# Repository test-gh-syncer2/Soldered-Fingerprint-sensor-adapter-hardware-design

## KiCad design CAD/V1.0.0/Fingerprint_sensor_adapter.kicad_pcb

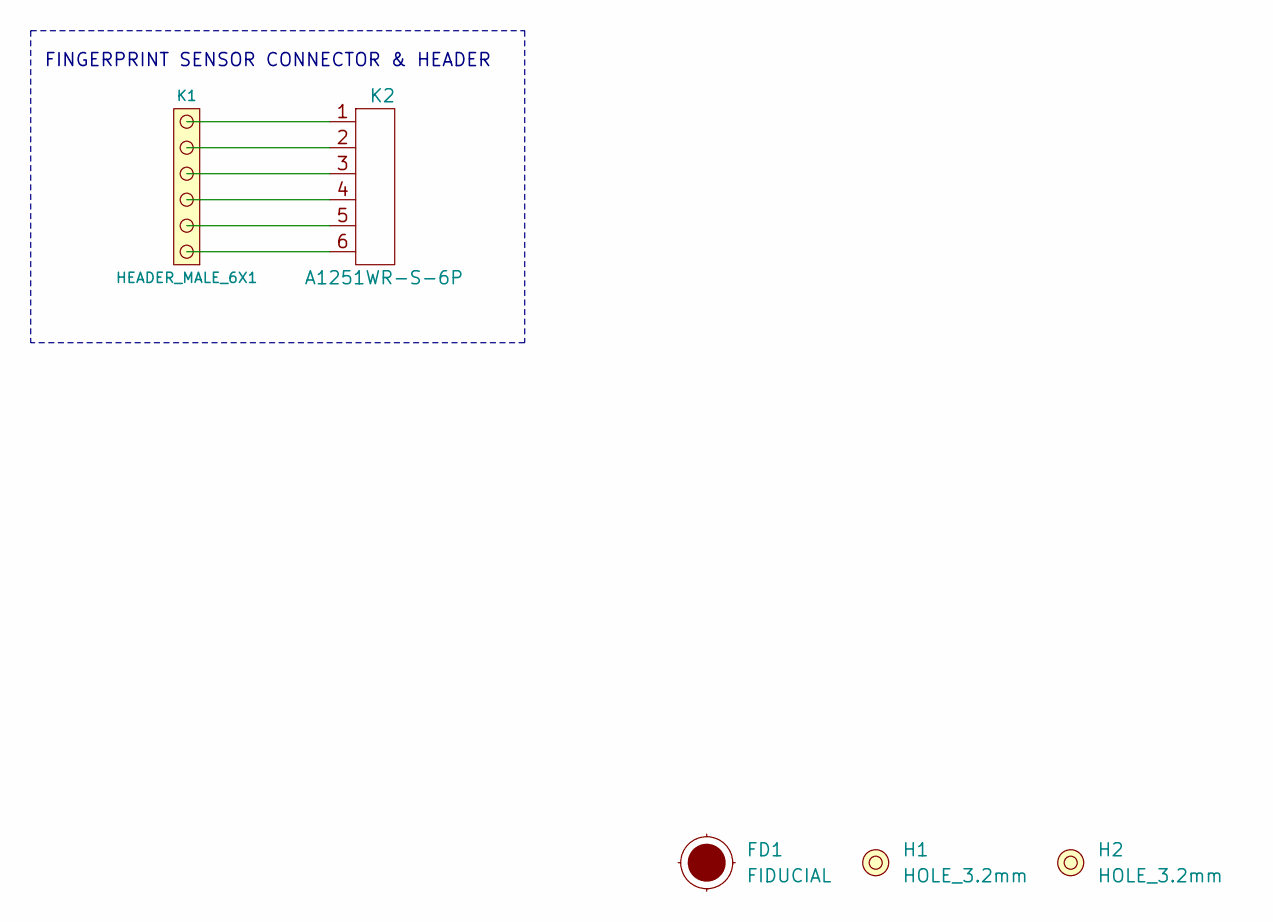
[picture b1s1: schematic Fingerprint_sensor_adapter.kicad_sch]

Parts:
FD1: FIDUCIAL; FIDUCIAL_23
H1, H2: HOLE_3.2mm
K1: HEADER_MALE_6X1
K2: A1251WR-S-6P

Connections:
unnamed: K1.1, K2.6
unnamed: K1.2, K2.5
unnamed: K1.3, K2.4
unnamed: K1.4, K2.3
unnamed: K1.5, K2.2
unnamed: K1.6, K2.1

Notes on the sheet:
FINGERPRINT SENSOR CONNECTOR & HEADER

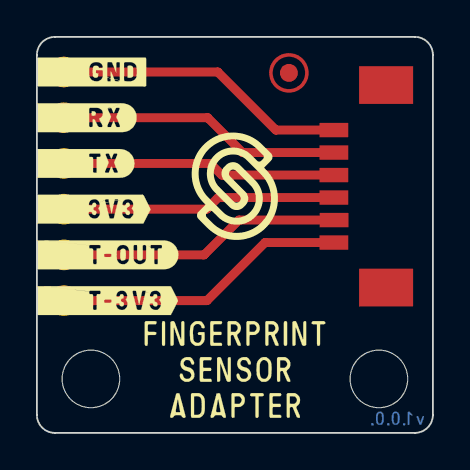
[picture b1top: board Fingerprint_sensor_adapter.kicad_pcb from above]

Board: 2 copper layers, 22.0 x 22.0 mm, 6 parts (1 on the bottom side), 6 nets.

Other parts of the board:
Ref**: Val**; Version1.0.0.

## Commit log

2021-09-23 Syncing to git
2021-09-23 Updating open source files.
